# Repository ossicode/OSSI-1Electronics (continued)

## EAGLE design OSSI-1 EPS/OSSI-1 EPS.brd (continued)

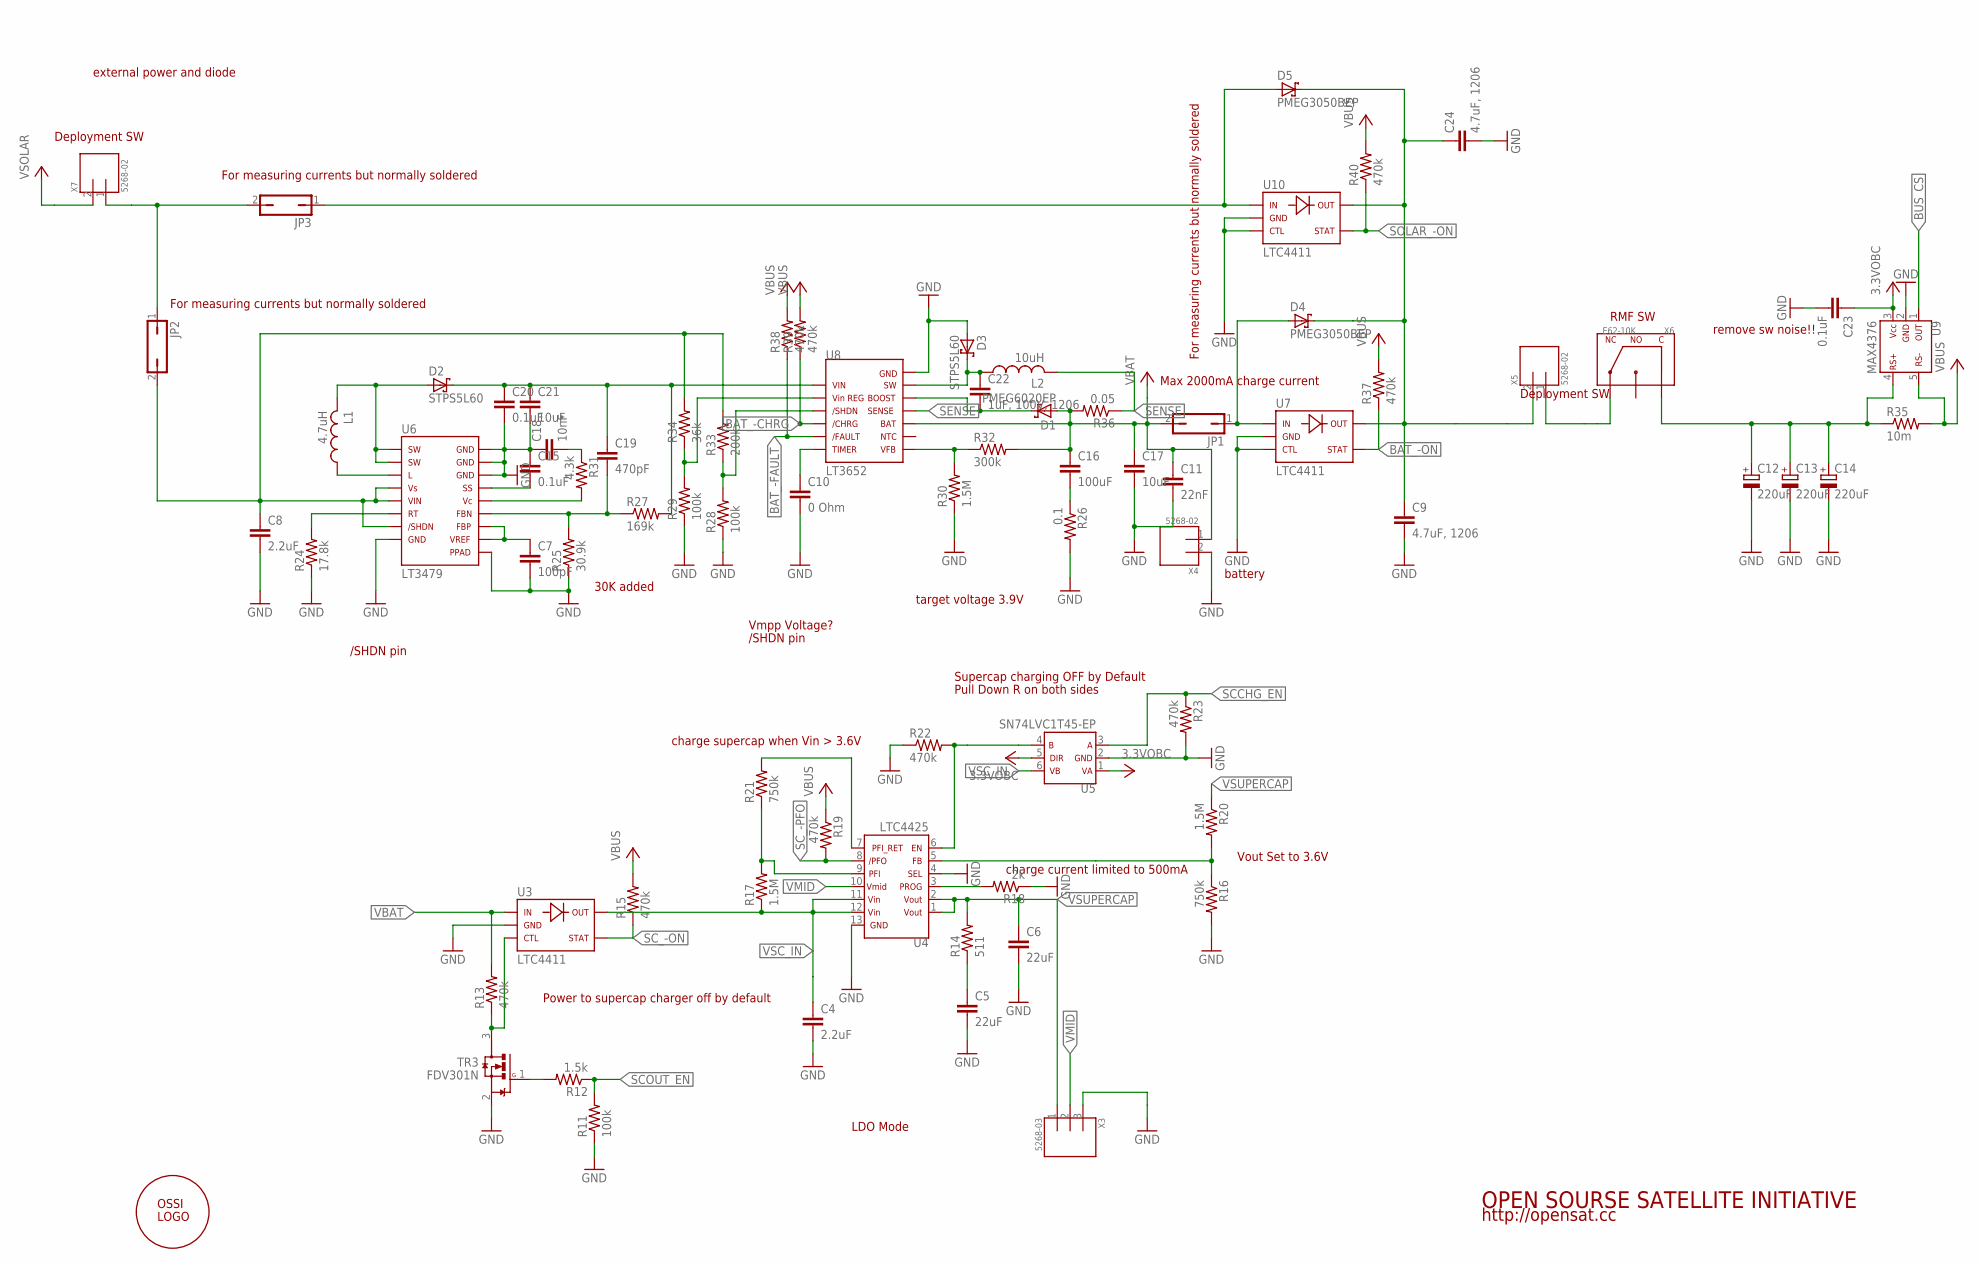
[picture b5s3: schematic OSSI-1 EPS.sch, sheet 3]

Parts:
C4, C8: 2.2uF; C1206-GCM31
C5, C6: 22uF; C1210-GCM32
C7: 100pF; C0603(1608)
C9, C24: 4.7uF, 1206; C1206-GCM31
C10: 0 Ohm; C0603(1608)
C11: 22nF; C0603(1608)
C12, C13, C14: 220uF; C2917(7343)-Y
C15, C20, C23: 0.1uF; C0603(1608)
C16: 100uF; C1210-TMK325
C17, C21: 10uF; C1210-GCM32
C18: 10nF; C0603(1608)
C19: 470pF; C0603(1608)
C22: 1uF, 100V, 1206; C0805(2012)
D1: PMEG6020EP
D2, D3: STPS5L60
D4, D5: PMEG3050BEP; PMEG6020EP
JP1, JP2, JP3: JP1Q; JP1
L1: 4.7uH; RLF7030
L2: 10uH; RLF12545
R11, R28, R29: 100k; R0603(1608)
R12: 1.5k; R0603(1608)
R13, R15, R19, R22, R23, R37, R38, R39, R40: 470k; R0603(1608)
R14: 511; WSL1206
R16, R21: 750k; R0603(1608)
R17, R20, R30: 1.5M; R0603(1608)
R18: 2k; R0603(1608)
R24: 17.8k; R0603(1608)
R25: 30.9k; R0603(1608)
R26: 0.1; WSL1206
R27: 169k; R0603(1608)
R31: 4.3k; R0603(1608)
R32: 300k; R0603(1608)
R33: 200k; R0603(1608)
R34: 36k; R0603(1608)
R35: 10m; WSL1206
R36: 0.05; WSL1206
TR3: FDV301N; SOT23
U3, U7, U10: LTC4411; TSOT23-5
U4: LTC4425; MSE
U5: SN74LVC1T45-EP; SOT-6DCK
U6: LT3479; TSSOP16-FE
U8: LT3652; MSE
U9: MAX4376; SOT23-5DBV
U$1: OSSILOGORECT; OSSILOGORECT1005
X3: 5268-03
X4, X5, X7: 5268-02; 5628-02
X6: E62-10K

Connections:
3.3VOBC: C23.1, U5.1, U5.5, U9.3; also elsewhere on the board
BAT_-CHRG: R39.1, U8.4; also elsewhere on the board
BAT_-FAULT: R38.1, U8.5; also elsewhere on the board
BAT_-ON: R37.1, U7.P$4; also elsewhere on the board
BUS_CS: U9.1; also elsewhere on the board
GND: C4.P$2 (2), C5.P$2 (2), C6.P$2 (2), C7.2, C8.P$2 (2), C9.P$2 (2), C10.2, C11.2, C12.2 (-), C13.2 (-), C14.2 (-), C15.1, C17.P$2 (2), C18.1, C20.2, C21.P$2 (2), C23.2, C24.P$2 (2), D3.A, R11.1, R16.2, R18.1, R22.1, R23.2, R24.1, R25.1, R26.P$2 (2), R28.1, R29.1, R30.1, TR3.2 (S), U3.P$2, U4.4, U4.13, U5.2, U6.8, U6.14, U6.15, U6.16, U6.PPAD, U7.P$2, U7.P$3, U8.13, U9.2, U10.P$2, U10.P$3, X3.3, X4.2; also elsewhere on the board
unnamed: L1.P$1 (1), U6.3
unnamed: R29.2, R34.1, U8.2
unnamed: C19.1, C20.1, C21.P$1 (1), D2.C, R27.2, U8.1
unnamed: C16.P$2 (2), R26.P$1 (1)
unnamed: C15.2, U6.13
unnamed: D2.A, L1.P$2 (2), U6.1, U6.2
unnamed: C18.2, R31.1
unnamed: R31.2, U6.12
unnamed: C19.2, R25.2, R27.1, U6.11
unnamed: C7.1, U6.9, U6.10
unnamed: R24.2, U6.6
unnamed: R28.2, R33.1, U8.3
unnamed: C22.2, D1.C, U8.11
unnamed: R16.1, R20.2, U4.5
unnamed: C22.1, D3.C, L2.P$1 (1), U8.12
unnamed: R30.2, R32.1, U8.7
unnamed: C9.P$1 (1), C24.P$1 (1), D4.C, D5.C, U7.P$5, U10.P$5, X5.2
unnamed: C10.1, U8.6
unnamed: R22.2, U4.6, U5.4
unnamed: C5.P$1 (1), R14.P$1 (1)
unnamed: R13.1, TR3.3 (D), U3.P$3
unnamed: R12.2, TR3.1 (G)
unnamed: C12.1 (+), C13.1 (+), C14.1 (+), R35.P$1 (1), U9.4, X6.C
unnamed: R17.2, R21.1, U4.9
unnamed: R21.2, U4.7
unnamed: D5.A, JP3.1, U10.P$1
unnamed: R18.2, U4.3
unnamed: D4.A, JP1.1, U7.P$1
unnamed: C8.P$1 (1), JP2.2, R33.2, R34.2, U6.4, U6.5, U6.7
unnamed: JP2.1, JP3.2, X7.1
unnamed: X5.1, X6.NC
SCCHG_EN: R23.1, U5.3; also elsewhere on the board
SCOUT_EN: R11.2, R12.1; also elsewhere on the board
SC_-ON: R15.1, U3.P$4; also elsewhere on the board
SC_-PFO: R19.2, U4.8; also elsewhere on the board
SENSE: L2.P$2 (2), R36.P$1 (1), U8.10
SOLAR_-ON: R40.1, U10.P$4; also elsewhere on the board
VBAT: C11.1, C16.P$1 (1), C17.P$1 (1), D1.A, JP1.2, R13.2, R32.2, R36.P$2 (2), U3.P$1, U8.9, X4.1; also elsewhere on the board
VBUS: R15.2, R19.1, R35.P$2 (2), R37.2, R38.2, R39.2, R40.2, U9.5; also elsewhere on the board
VMID: U4.10, X3.2
VSC_IN: C4.P$1 (1), R17.1, U3.P$5, U4.11, U4.12, U5.6
VSOLAR: X7.2; also elsewhere on the board
VSUPERCAP: C6.P$1 (1), R14.P$2 (2), R20.1, U4.1, U4.2, X3.1; also elsewhere on the board

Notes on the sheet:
/SHDN pin
Vmpp Voltage?
Max 2000mA charge current
target voltage 3.9V
Deployment SW
RMF SW
external power and diode
remove sw noise!!
battery
LDO Mode
Vout Set to 3.6V
Supercap charging OFF by Default
Pull Down R on both sides
charge current limited to 500mA
charge supercap when Vin > 3.6V
Power to supercap charger off by default
30K added
For measuring currents but normally soldered
OPEN SOURSE SATELLITE INITIATIVE
http://opensat.cc

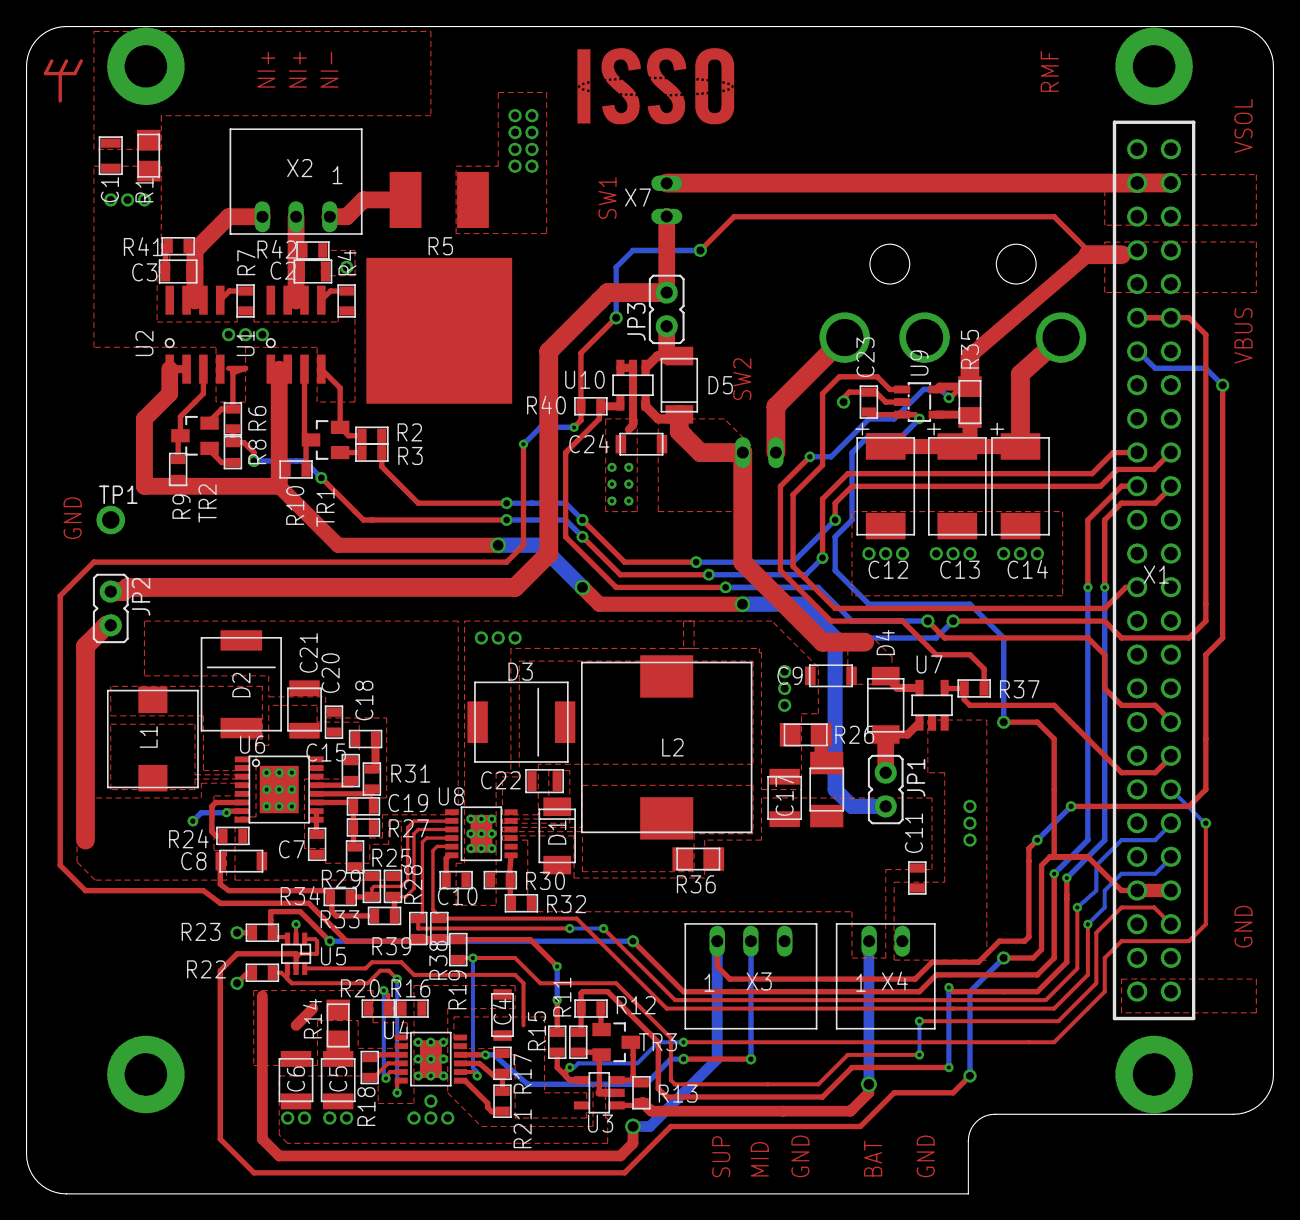
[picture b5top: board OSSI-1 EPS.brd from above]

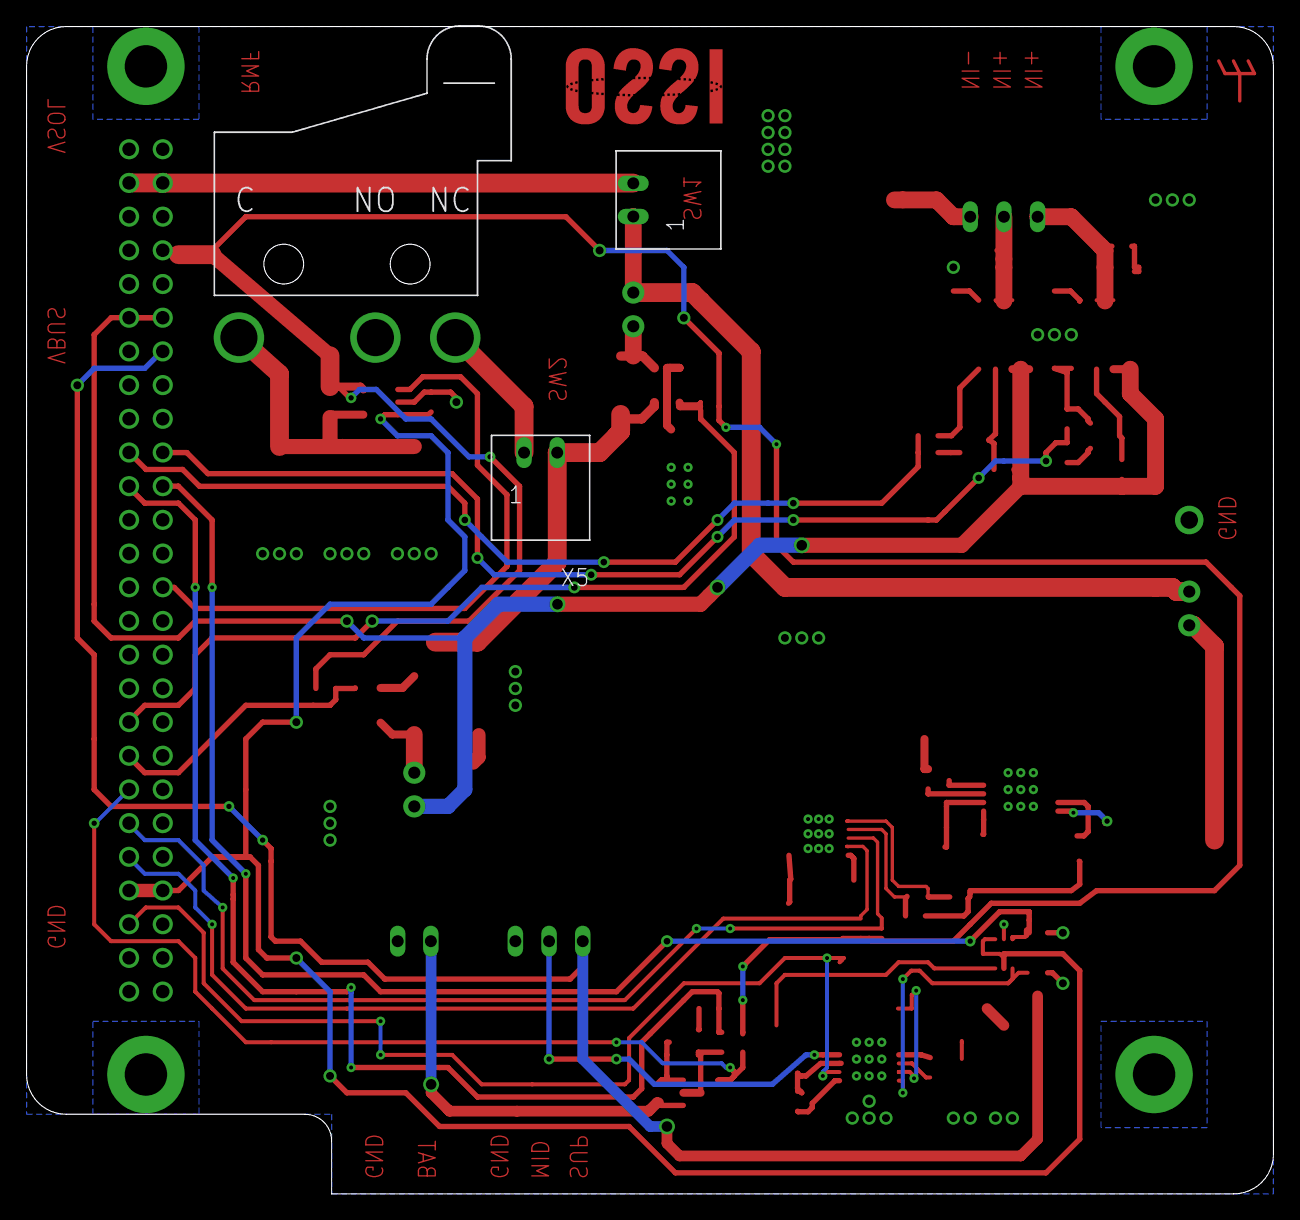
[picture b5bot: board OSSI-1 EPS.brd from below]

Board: 2 copper layers, 94.0 x 88.0 mm, 102 parts (3 on the bottom side), 61 nets.

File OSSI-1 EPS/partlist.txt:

Partlist

Exported from OSSIEPSNew.sch at 2013-02-27 ¿ÀÀü 1:14:43

EAGLE Version 6.1.0 Copyright (c) 1988-2012 CadSoft

Assembly variant: 

Part     Value              Device             Package        Library  Sheet

C1                          C0805(2012)        C0805(2012)    OSSI     1
C2       100nF, 0805        C0805(2012)        C0805(2012)    OSSI     2
C3       100nF, 0805        C0805(2012)        C0805(2012)    OSSI     2
C4       2.2uF              C1206(3216)-GCM31  C1206-GCM31    OSSI     3
C5       22uF               C1210(3225)-GCM32  C1210-GCM32    OSSI     3
C6       22uF               C1210(3225)-GCM32  C1210-GCM32    OSSI     3
C7       100pF              C0603(1608)        C0603(1608)    OSSI     3
C8       2.2uF              C1206(3216)-GCM31  C1206-GCM31    OSSI     3
C9       4.7uF, 1206        C1206(3216)-GCM31  C1206-GCM31    OSSI     3
C10      0 Ohm              C0603(1608)        C0603(1608)    OSSI     3
C11                         C0603(1608)        C0603(1608)    OSSI     3
C12      220uF              C-TANTAL-Y         C2917(7343)-Y  OSSI     3
C13      220uF              C-TANTAL-Y         C2917(7343)-Y  OSSI     3
C14      220uF              C-TANTAL-Y         C2917(7343)-Y  OSSI     3
C15      0.1uF              C0603(1608)        C0603(1608)    OSSI     3
C16      100uF              C1210(3225)-TMK325 C1210-TMK325   OSSI     3
C17      10uF               C1210(3225)-GCM32  C1210-GCM32    OSSI     3
C18      10nF               C0603(1608)        C0603(1608)    OSSI     3
C19      470pF              C0603(1608)        C0603(1608)    OSSI     3
C20      0.1uF              C0603(1608)        C0603(1608)    OSSI     3
C21      10uF               C1210(3225)-GCM32  C1210-GCM32    OSSI     3
C22      1uF, 100V          C0805(2012)        C0805(2012)    OSSI     3
C23      0.1uF              C0603(1608)        C0603(1608)    OSSI     3
C24      4.7uF, 1206        C1206(3216)-GCM31  C1206-GCM31    OSSI     3
D1       PMEG6020EP         PMEG6020EP         PMEG6020EP     OSSI     3
D2       STPS5L60           STPS5L60           STPS5L60       OSSI     3
D3       STPS5L60           STPS5L60           STPS5L60       OSSI     3
D4       PMEG6020EP         PMEG6020EP         PMEG6020EP     OSSI     3
D5       PMEG6020EP         PMEG6020EP         PMEG6020EP     OSSI     3
H1       MOUNT-PAD-ROUND3.2 MOUNT-PAD-ROUND3.2 3.2-PAD-ROUND  OSSI     1
H2       MOUNT-PAD-ROUND3.2 MOUNT-PAD-ROUND3.2 3.2-PAD-ROUND  OSSI     1
H3       MOUNT-PAD-ROUND3.2 MOUNT-PAD-ROUND3.2 3.2-PAD-ROUND  OSSI     1
H4       MOUNT-PAD-ROUND3.2 MOUNT-PAD-ROUND3.2 3.2-PAD-ROUND  OSSI     1
JP1                         JP1Q               JP1            OSSI     3
JP2                         JP1Q               JP1            OSSI     3
JP3                         JP1Q               JP1            OSSI     3
L1       4.7uH              LRLF7030           RLF7030        OSSI     3
L2       10uH               LRLF12545          RLF12545       OSSI     3
R1       511                RWSL1206           WSL1206        OSSI     1
R2       47k                R0603(1608)        R0603(1608)    OSSI     2
R3       1.5k               R0603(1608)        R0603(1608)    OSSI     2
R4       1.2k               R0603(1608)        R0603(1608)    OSSI     2
R5       1R5, 20W, 1%       RPWR263S           PWR263S-20     OSSI     2
R6       47k                R0603(1608)        R0603(1608)    OSSI     2
R7       1.2k               R0603(1608)        R0603(1608)    OSSI     2
R8       1.5k               R0603(1608)        R0603(1608)    OSSI     2
R9       100k               R0603(1608)        R0603(1608)    OSSI     2
R10      100k               R0603(1608)        R0603(1608)    OSSI     2
R11      47k                R0603(1608)        R0603(1608)    OSSI     3
R12      1.5k               R0603(1608)        R0603(1608)    OSSI     3
R13      470k               R0603(1608)        R0603(1608)    OSSI     3
R14      511                RWSL1206           WSL1206        OSSI     3
R15      470k               R0603(1608)        R0603(1608)    OSSI     3
R16      750k               R0603(1608)        R0603(1608)    OSSI     3
R17      1.5M               R0603(1608)        R0603(1608)    OSSI     3
R18      2k                 R0603(1608)        R0603(1608)    OSSI     3
R19      470k               R0603(1608)        R0603(1608)    OSSI     3
R20      1.5M               R0603(1608)        R0603(1608)    OSSI     3
R21      750k               R0603(1608)        R0603(1608)    OSSI     3
R22      470k               R0603(1608)        R0603(1608)    OSSI     3
R23      470k               R0603(1608)        R0603(1608)    OSSI     3
R24      17.8k              R0603(1608)        R0603(1608)    OSSI     3
R25      30.9k              R0603(1608)        R0603(1608)    OSSI     3
R26      0.1                RWSL1206           WSL1206        OSSI     3
R27      169k               R0603(1608)        R0603(1608)    OSSI     3
R28      100k               R0603(1608)        R0603(1608)    OSSI     3
R29      100k               R0603(1608)        R0603(1608)    OSSI     3
R30      1.5M               R0603(1608)        R0603(1608)    OSSI     3
R31      4.3k               R0603(1608)        R0603(1608)    OSSI     3
R32      300k               R0603(1608)        R0603(1608)    OSSI     3
R33      200k               R0603(1608)        R0603(1608)    OSSI     3
R34      36k                R0603(1608)        R0603(1608)    OSSI     3
R35      20m / 10m          RWSL1206           WSL1206        OSSI     3
R36      0.05               RWSL1206           WSL1206        OSSI     3
R37      470k               R0603(1608)        R0603(1608)    OSSI     3
R38      470k               R0603(1608)        R0603(1608)    OSSI     3
R39      470k               R0603(1608)        R0603(1608)    OSSI     3
R40      470k               R0603(1608)        R0603(1608)    OSSI     3
TP1      TP                 TP                 TP-13          OSSI     1
TR1      FDV301N            FDV301N            SOT23          OSSI     2
TR2      FDV301N            FDV301N            SOT23          OSSI     2
TR3      FDV301N            FDV301N            SOT23          OSSI     3
U1       MAX890L            MAX890L            SO8            OSSI     2
U2       MAX890L            MAX890L            SO8            OSSI     2
U3       LTC4411            LTC4411            TSOT23-5       OSSI     3
U4       LTC4425            LTC4425            MSE            OSSI     3
U5       SN74LVC1T45-EP     SN74LVC1T45-EP     SOT-6DCK       OSSI     3
U6       LT3479             LT3479             TSSOP16-FE     OSSI     3
U7       LTC4411            LTC4411            TSOT23-5       OSSI     3
U8       LT3652             LT3652             MSE            OSSI     3
U9       MAX4376            MAX4376            SOT23-5DBV     OSSI     3
U10      LTC4411            LTC4411            TSOT23-5       OSSI     3
X1       ESQ-126-38-G-D     ESQ-126-38-G-D     ESQ-126-XX-X-D OSSI     1
X2       5268-03            5268-03            5268-03        OSSI     2
X3       5268-03            5268-03            5268-03        OSSI     3
X4       5268-02            5268-02            5628-02        OSSI     3
X5       5268-02            5268-02            5628-02        OSSI     3
X6       E62-10K            E62-10K            E62-10K        OSSI     3
X7       5268-02            5268-02            5628-02        OSSI     3

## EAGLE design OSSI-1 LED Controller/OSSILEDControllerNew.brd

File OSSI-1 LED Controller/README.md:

### OSSI-1 Satellite LED Controller Module

**LED Controller Module is responsible for controlling 44W high power LEDs powered from supercapacitors.**  

Mainly Eagle 6.1 / 6.5 version  
Please, see the comments from the schematic file for more information.  
Block diagram and rationale behind the design will be provided with video turorial soon.  

Open Source Satellite Initiative http://opensat.cc

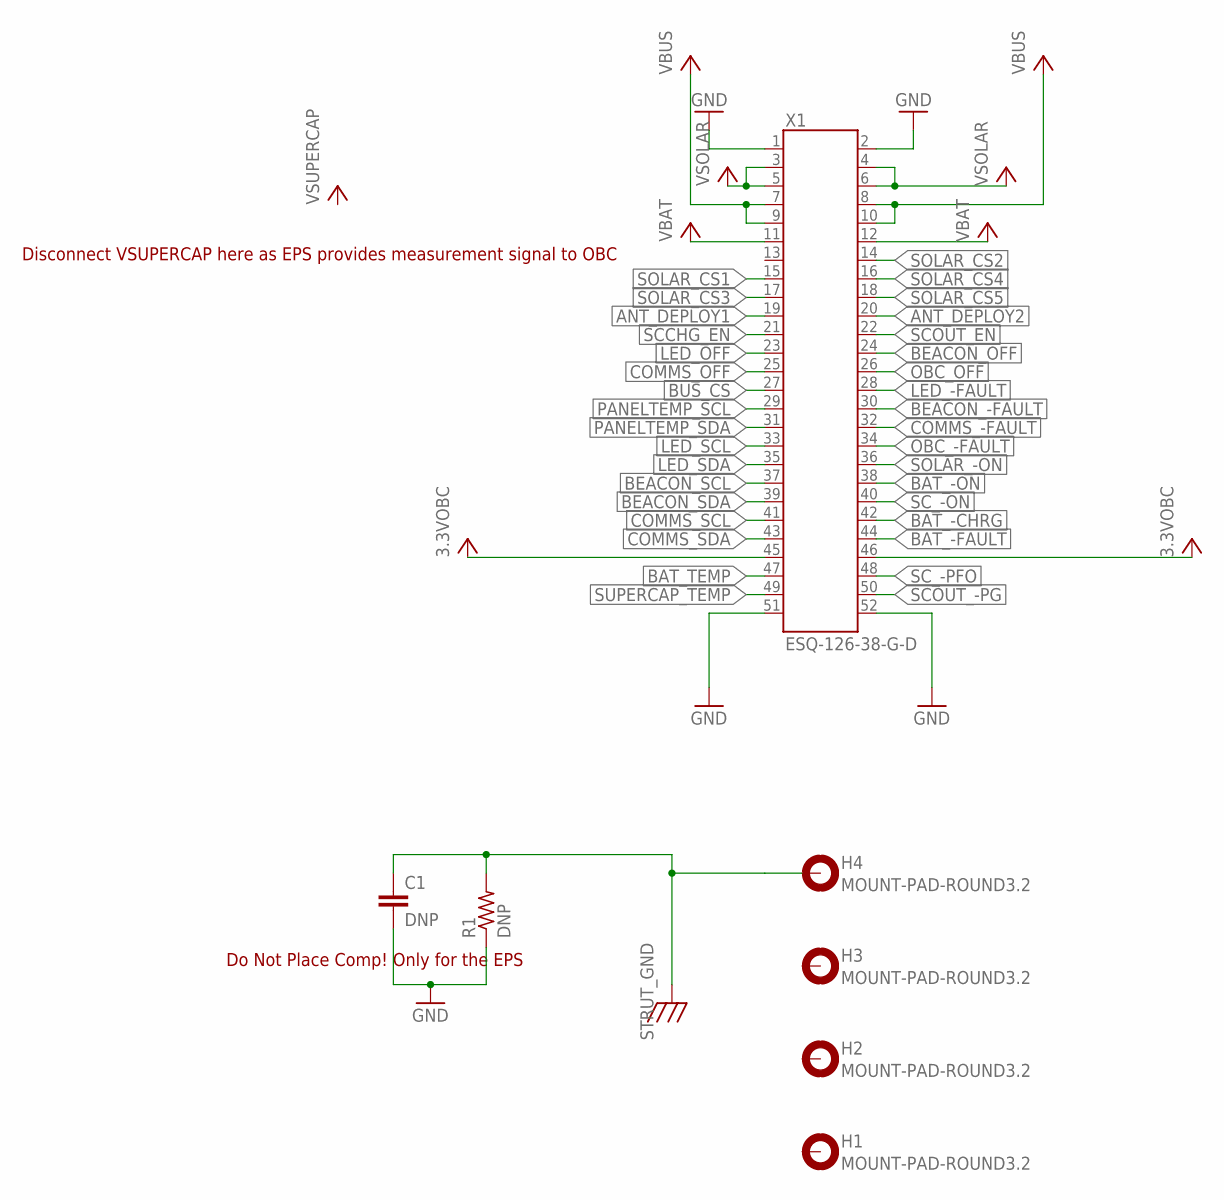
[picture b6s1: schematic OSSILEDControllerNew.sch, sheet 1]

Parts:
C1: DNP; C0805(2012)
H1, H2, H3, H4: MOUNT-PAD-ROUND3.2; 3.2-PAD-ROUND
R1: DNP; WSL1206
X1: ESQ-126-38-G-D; ESQ-126-XX-X-D

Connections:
3.3VOBC: X1.45, X1.46
ANT_DEPLOY1: X1.19
ANT_DEPLOY2: X1.20
BAT_-CHRG: X1.42
BAT_-FAULT: X1.44
BAT_-ON: X1.38
BAT_TEMP: X1.47
BEACON_-FAULT: X1.30
BEACON_OFF: X1.24
BEACON_SCL: X1.37
BEACON_SDA: X1.39
BUS_CS: X1.27
COMMS_-FAULT: X1.32
COMMS_OFF: X1.25
COMMS_SCL: X1.41
COMMS_SDA: X1.43
GND: C1.2, R1.P$1 (1), X1.1, X1.2, X1.51, X1.52; also elsewhere on the board
LED_-FAULT: X1.28; also elsewhere on the board
LED_OFF: X1.23; also elsewhere on the board
LED_SCL: X1.33; also elsewhere on the board
LED_SDA: X1.35; also elsewhere on the board
OBC_-FAULT: X1.34
OBC_OFF: X1.26
PANELTEMP_SCL: X1.29
PANELTEMP_SDA: X1.31
SCCHG_EN: X1.21
SCOUT_-PG: X1.50
SCOUT_EN: X1.22
SC_-ON: X1.40
SC_-PFO: X1.48
SOLAR_-ON: X1.36
SOLAR_CS1: X1.15
SOLAR_CS2: X1.14
SOLAR_CS3: X1.17
SOLAR_CS4: X1.16
SOLAR_CS5: X1.18
STRUT_GND: C1.1, H4.B3,2, R1.P$2 (2)
SUPERCAP_TEMP: X1.49
VBAT: X1.11, X1.12
VBUS: X1.7, X1.8, X1.9, X1.10; also elsewhere on the board
VSOLAR: X1.3, X1.4, X1.5, X1.6

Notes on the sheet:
Disconnect VSUPERCAP here as EPS provides measurement signal to OBC
Do Not Place Comp! Only for the EPS

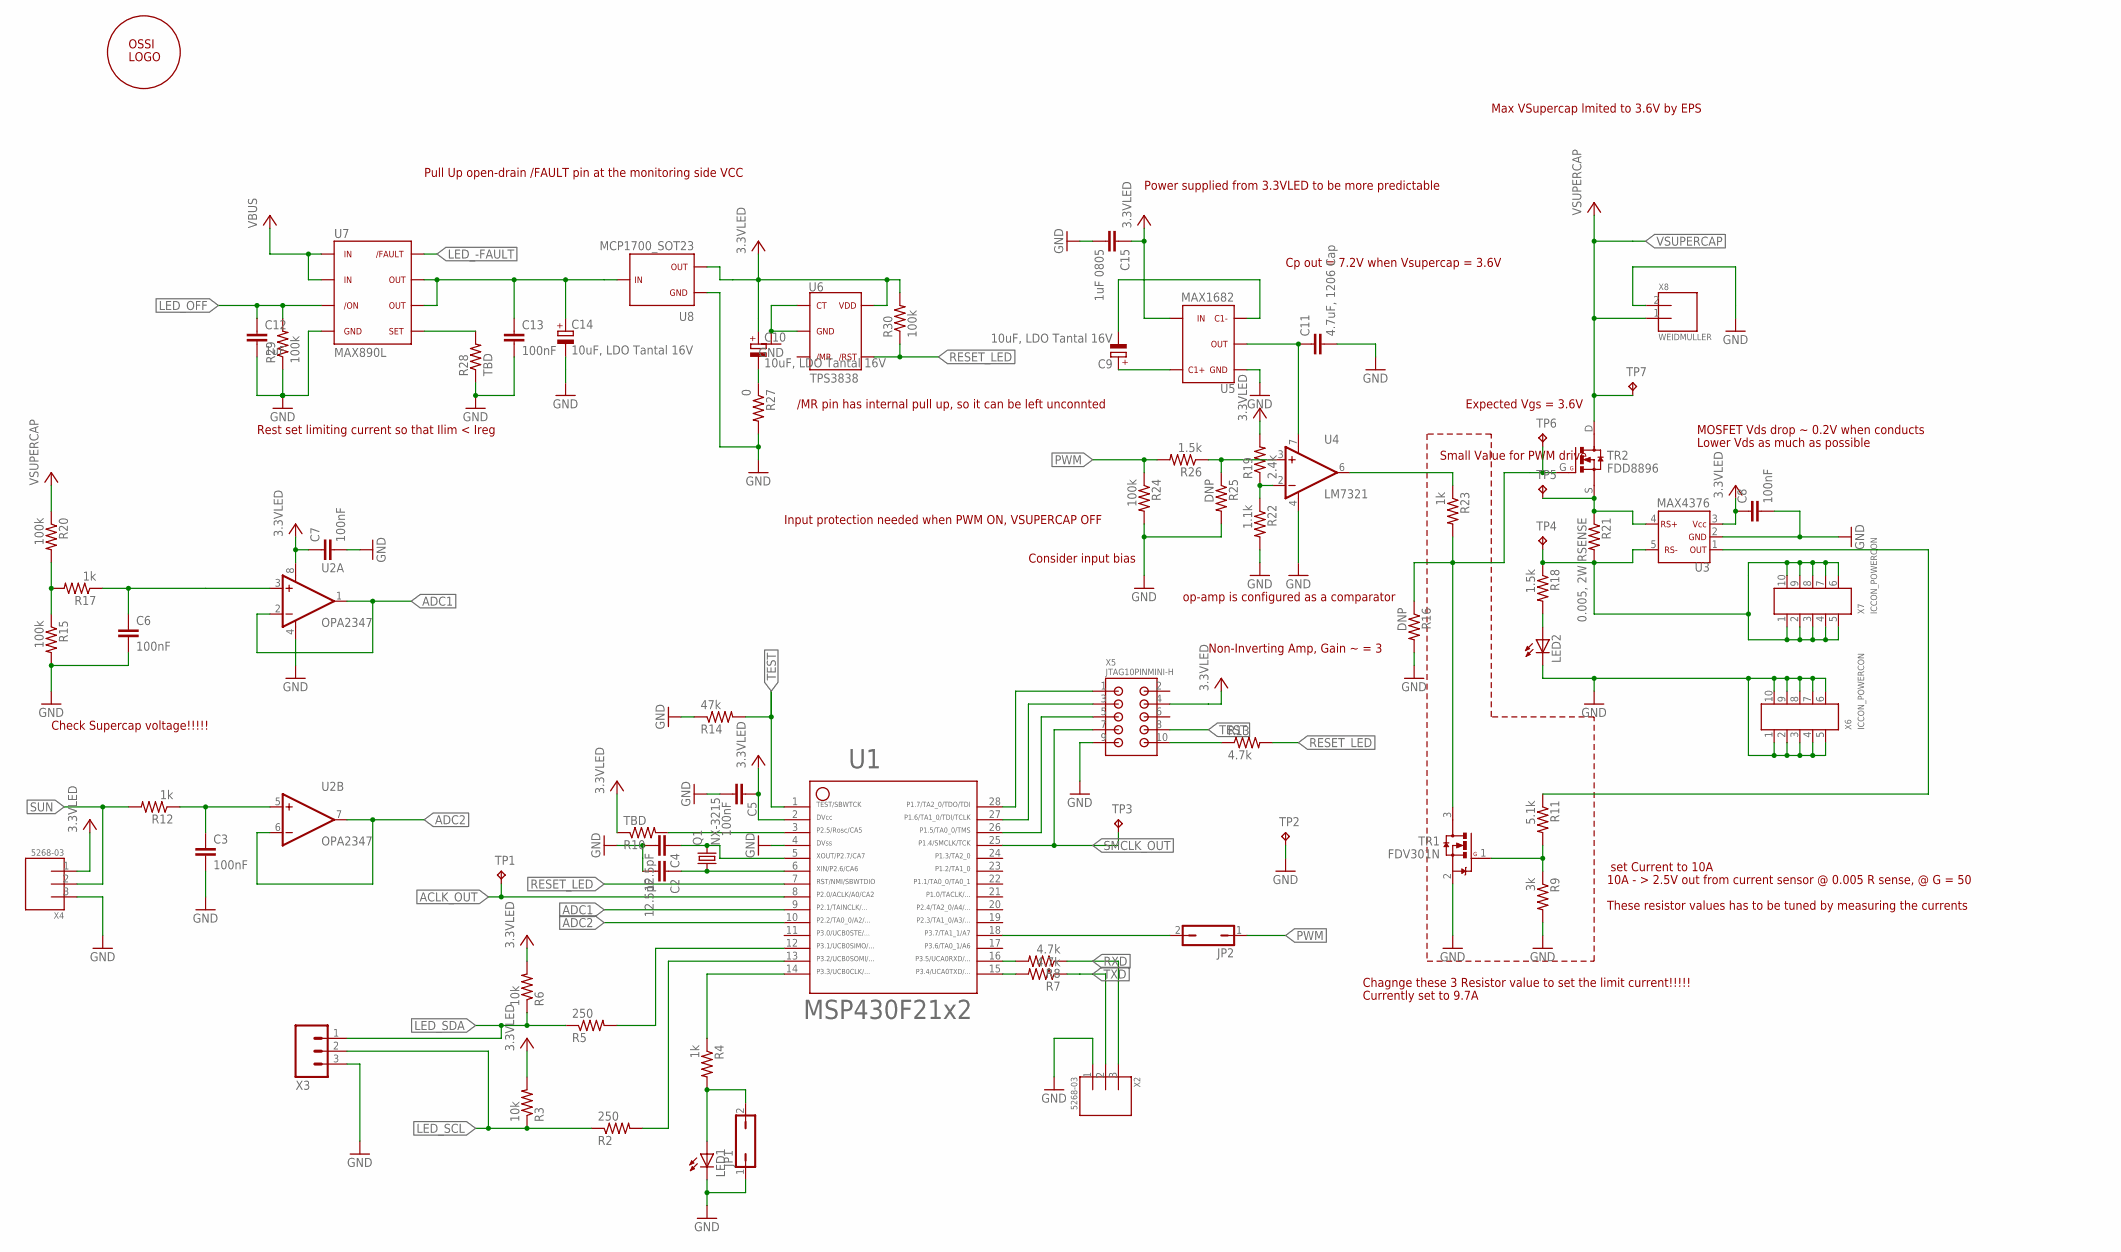
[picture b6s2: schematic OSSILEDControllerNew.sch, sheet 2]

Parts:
C2, C4: 12.5pF; C0603(1608)
C3, C5, C6, C7, C8, C13: 100nF; C0603(1608)
C9, C10, C14: 10uF, LDO Tantal 16V; C1206(3216)-A
C11: 4.7uF, 1206 Cap; C1206-GCM31
C12: 1uF; C0603(1608)
C15: 1uF 0805; C0805(2012)
JP1, JP2: JP1Q; JP1
LED1: LED0603; LED-0603
LED2: LEDCHIPLED_0603; CHIPLED_0603
Q1: NX-3215
R2, R5: 250; R0603(1608)
R3, R6: 10k; R0603(1608)
R4, R12, R17, R23: 1k; R0603(1608)
R7, R8, R13: 4.7k; R0603(1608)
R9: 3k; R0603(1608)
R10, R28: TBD; R0603(1608)
R11: 5.1k; R0603(1608)
R14: 47k; R0603(1608)
R15, R20, R24, R29, R30: 100k; R0603(1608)
R16, R25: DNP; R0603(1608)
R18, R26: 1.5k; R0603(1608)
R19: 2.4k; R0603(1608)
R21: 0.005, 2W RSENSE; R4527(12070)
R22: 1.1k; R0603(1608)
R27: 0; R0603(1608)
TP1, TP2, TP3, TP4, TP5, TP6, TP7: TP; TP-13
TR1: FDV301N; SOT23
TR2: FDD8896; TO252
U1: MSP430F2132; PW28
U2: OPA2347; SOT23-8DCN
U3: MAX4376; SOT23-5DBV
U4: LM7321; SO8
U5: MAX1682; SOT23-5DBV
U6: TPS3838; SOT23-5DBV
U7: MAX890L; SO8
U8: MCP1700_SOT23; SOT23
U$: OSSILOGORECT; OSSILOGORECT1005
X2, X4: 5268-03
X3: M03PTH; 1X03
X5: JTAG10PINMINI-H; M50-3200545
X6, X7: ICCON_POWERCON; ICCON6643220-1
X8: WEIDMULLER; WEIDMULLER1760490000

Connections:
3.3VLED: C5.1, C7.1, C8.1, C10.1 (+), C15.1, R3.2, R6.2, R10.1, R19.2, R30.2, U1.2, U2.8 (V+), U3.3, U5.4, U6.5, U8.2, X4.1, X5.4
ACLK_OUT: TP1.TP, U1.8
ADC1: U1.9, U2.1 (OUT), U2.2 (-IN)
ADC2: U1.10, U2.6 (-IN), U2.7 (OUT)
GND: C2.2, C3.2, C4.2, C5.2, C6.2, C7.2, C8.2, C11.P$2 (2), C12.2, C13.2, C14.2 (-), C15.2, JP1.1, LED1.C, LED2.C, R9.2, R14.1, R15.2, R16.2, R22.2, R24.2, R25.2, R27.2, R28.1, R29.1, TP2.TP, TR1.2 (S), U1.4, U2.4 (V-), U3.2, U4.4 (V-), U5.1, U6.1, U6.2, U7.4, U8.1, X2.1, X3.3, X4.3, X5.9, X6.1, X6.2, X6.3, X6.4, X6.5, X6.6, X6.7, X6.8, X6.9, X6.10, X8.2; also elsewhere on the board
LED_-FAULT: U7.8; also elsewhere on the board
LED_OFF: C12.1, R29.2, U7.3; also elsewhere on the board
LED_SCL: R2.1, R3.1, X3.2; also elsewhere on the board
LED_SDA: R5.1, R6.1, X3.1; also elsewhere on the board
unnamed: U1.28, X5.1
unnamed: R10.2, U1.3
unnamed: C13.1, C14.1 (+), U7.6, U7.7, U8.3
unnamed: R16.1, R23.2, TP6.TP, TR1.3 (D), TR2.G
unnamed: C6.1, R17.1, U2.3 (+IN)
unnamed: C3.1, R12.1, U2.5 (+IN)
unnamed: R25.1, R26.1, U4.3 (+IN)
unnamed: R28.2, U7.5
unnamed: R15.1, R17.2, R20.2
unnamed: R18.1, R21.P$2 (2), TP4.TP, U3.5, X7.1, X7.2, X7.3, X7.4, X7.5, X7.6, X7.7, X7.8, X7.9, X7.10
unnamed: C11.P$1 (1), U4.7 (V+), U5.2
unnamed: R23.1, U4.6 (OUT)
unnamed: U1.27, X5.3
unnamed: R21.P$1 (1), TP5.TP, TR2.S, U3.4
unnamed: C10.2 (-), R27.1
unnamed: R19.1, R22.1, U4.2 (-IN)
unnamed: C4.1, Q1.2, U1.5
unnamed: C2.1, Q1.1, U1.6
unnamed: JP1.2, LED1.A, R4.2
unnamed: R5.2, U1.12
unnamed: R2.2, U1.13
unnamed: R11.1, U3.1
unnamed: R4.1, U1.14
unnamed: C9.2 (-), U5.3
unnamed: C9.1 (+), U5.5
unnamed: R8.2, U1.16
unnamed: LED2.A, R18.2
unnamed: R9.1, R11.2, TR1.1 (G)
unnamed: U1.26, X5.5
unnamed: R13.1, X5.10
unnamed: JP2.2, U1.18
unnamed: R7.2, U1.15
PWM: JP2.1, R24.1, R26.2
RESET_LED: R13.2, R30.1, U1.7, U6.4
RXD: R8.1, X2.3
SMCLK_OUT: TP3.TP, U1.25, X5.7
SUN: R12.2, X4.2
TEST: R14.2, U1.1, X5.8
TXD: R7.1, X2.2
VBUS: U7.1, U7.2; also elsewhere on the board
VSUPERCAP: R20.1, TP7.TP, TR2.D, X8.1

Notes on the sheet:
Rest set limiting current so that Ilim < Ireg
Pull Up open-drain /FAULT pin at the monitoring side VCC
/MR pin has internal pull up, so it can be left unconnted
Check Supercap voltage!!!!!
Non-Inverting Amp, Gain ~ = 3
set Current to 10A
10A - > 2.5V out from current sensor @ 0.005 R sense, @ G = 50
Chagnge these 3 Resistor value to set the limit current!!!!!
Expected Vgs = 3.6V
Max VSupercap lmited to 3.6V by EPS
Cp out = 7.2V when Vsupercap = 3.6V
Input protection needed when PWM ON, VSUPERCAP OFF
Currently set to 9.7A
op-amp is configured as a comparator
Power supplied from 3.3VLED to be more predictable
These resistor values has to be tuned by measuring the currents
Small Value for PWM drive
MOSFET Vds drop ~ 0.2V when conducts
Lower Vds as much as possible
Consider input bias
